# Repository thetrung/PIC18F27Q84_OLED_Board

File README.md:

PIC18F27Q84 OLED Playboard
==============================
Nothing much to say, just for entertainment & satisfy myself for designing things in my head.

### Overview ::
**MCU SPECS:** 64Mhz - 128KB Flash - 8KB SRAM - 1KB EEPROM. 
Detailed information on [Microchip](https://www.microchip.com/en-us/product/pic18f27q43).

The board was made with intention to resemble tiny game consoles with proper input / output, which I got inspired by ATTiny85 board. It has :

- 1x Speaker
- 1x Power slide.
- 4x Buttons Input.
- 10x LEDs on Top Row.
- 4x LEDs above all buttons.
- 1x LEDs to indicate power state.
- 1x LED for STATUS (anything you want).
- ICSP to Program with Microchip PICKIT 3/4/5.
- OLED 128x32 Module support pins (SDA/SCK/VCC/GND).

- The 3V Battery Holder can be installed on the back. Although I'm not sure if it can actually run since got nothing to test but any compatible coin-battery should work somehow (CR2032, LIR2032... but I aim for CR2450). Turn off any unused / unnecessary modules inside your PIC & outside the board to save power on battery. I only tested this dual power system via simulator mostly :

### Schematic ::

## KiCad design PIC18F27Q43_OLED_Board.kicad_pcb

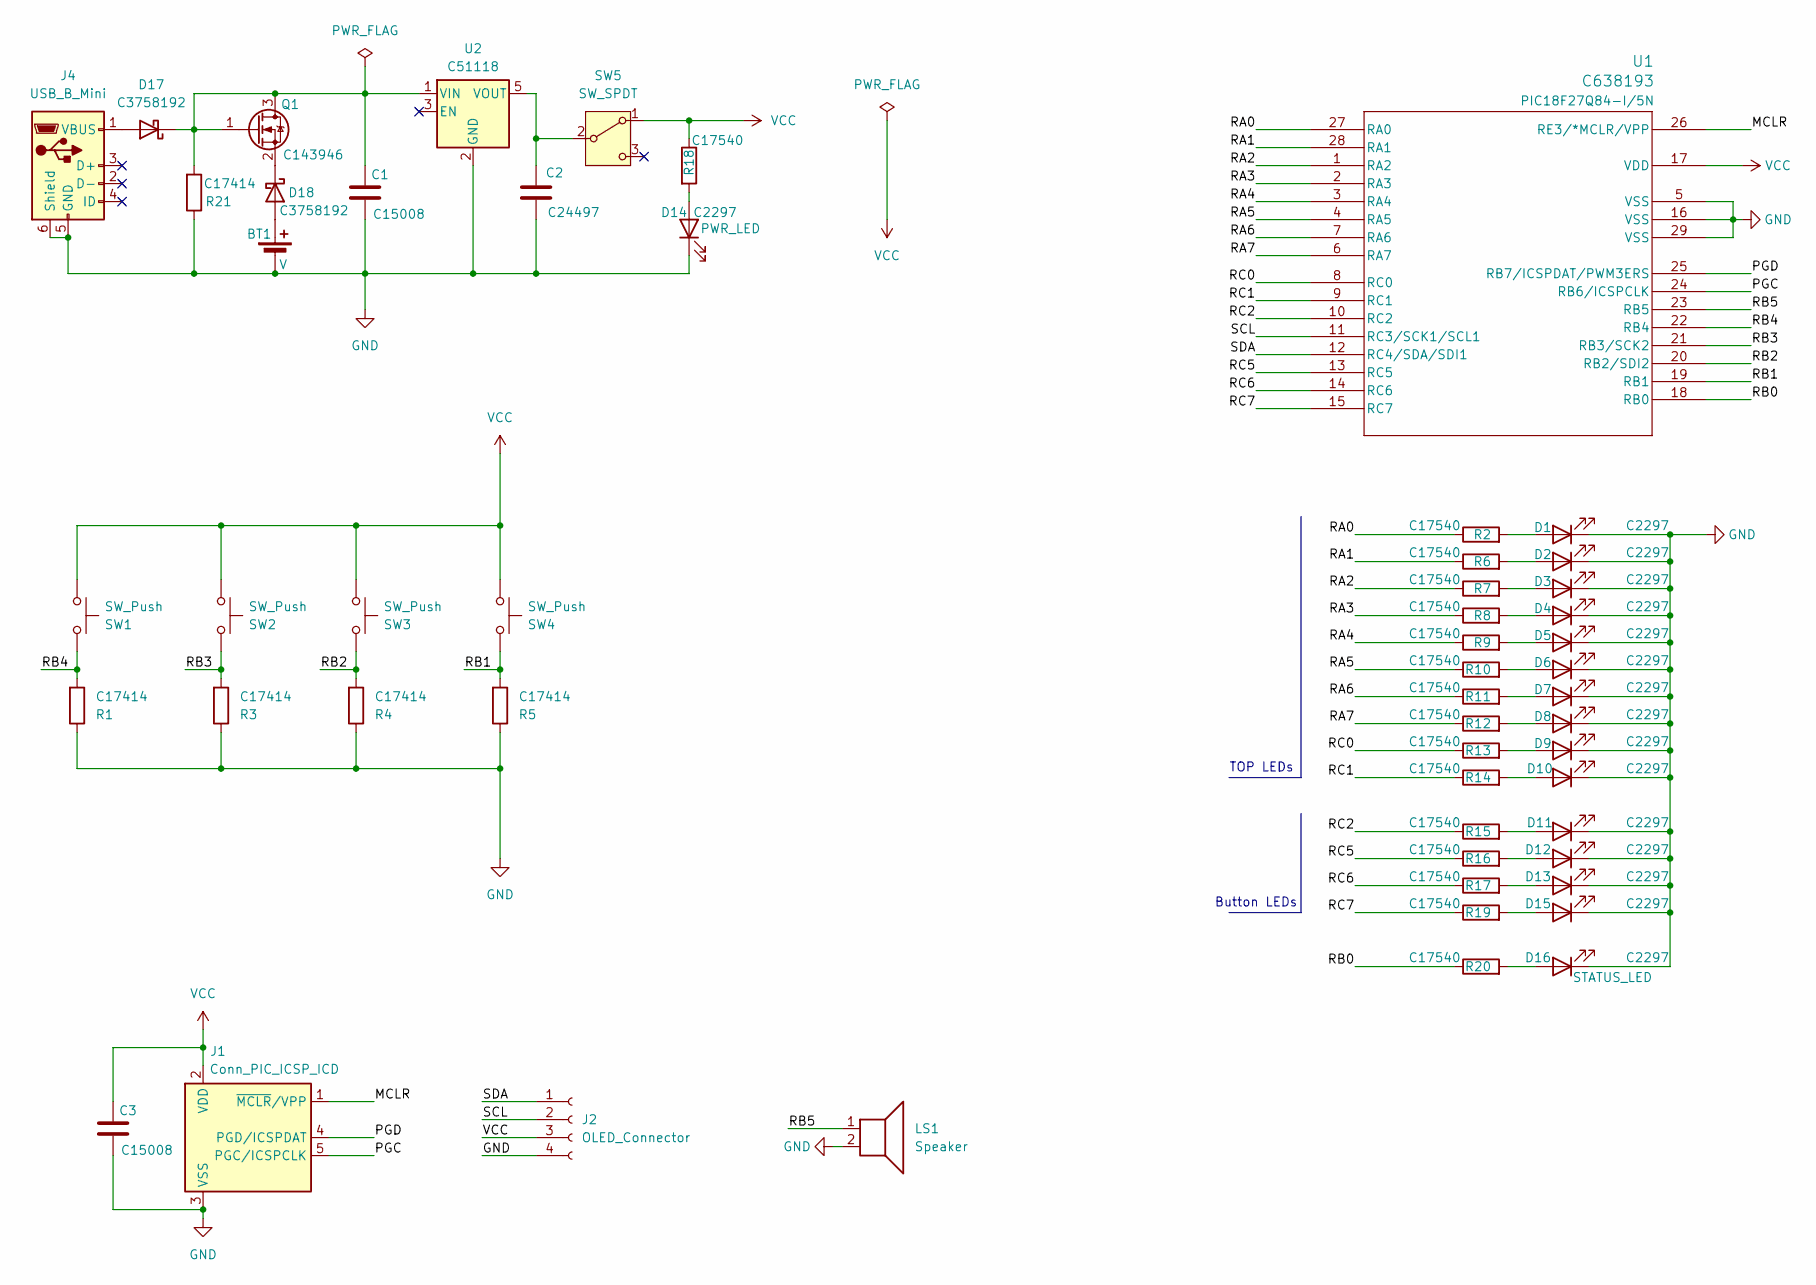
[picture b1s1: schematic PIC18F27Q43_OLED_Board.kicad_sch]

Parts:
BT1: V; BatteryHolder_ComfortableElectronic_CH273-2450_1x2450
C1, C3: C15008; C_1206_3216Metric
C2: C24497; C_1206_3216Metric
D1, D2, D3, D4, D5, D6, D7, D8, D9, D10, D11, D12, D13, D14, D15, D16: C2297; LED_0805_2012Metric
D17, D18: C3758192; D_0603_1608Metric
J1: Conn_PIC_ICSP_ICD; PinHeader_1x05_P2.54mm_Vertical
J2: OLED_Connector; PinHeader_1x04_P2.54mm_Vertical
J4: USB_B_Mini; USB_Mini-B_Tensility_54-00023_Vertical
LS1: Speaker; Buzzer_12x9.5RM7.6
Q1: C143946; SOT-23
R1, R3, R4, R5, R21: C17414; R_0805_2012Metric
R2, R6, R7, R8, R9, R10, R11, R12, R13, R14, R15, R16, R17, R18, R19, R20: C17540; R_0805_2012Metric
SW1, SW2, SW3, SW4: SW_Push; SW_PUSH_6mm_H5mm
SW5: SW_SPDT; SW_Slide_SPDT_Straight_CK_OS102011MS2Q
U1: C638193; VQFN28_5N_MCH
U2: C51118; SOT-23-5

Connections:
/MCLR: J1.1 (~MCLR/VPP), U1.26 (RE3/*MCLR/VPP)
/PGC: J1.5 (PGC/ICSPCLK), U1.24 (RB6/ICSPCLK)
/PGD: J1.4 (PGD/ICSPDAT), U1.25 (RB7/ICSPDAT/PWM3ERS)
/RA0: R2.1, U1.27 (RA0)
/RA1: R6.1, U1.28 (RA1)
/RA2: R7.1, U1.1 (RA2)
/RA3: R8.1, U1.2 (RA3)
/RA4: R9.1, U1.3 (RA4)
/RA5: R10.1, U1.4 (RA5)
/RA6: R11.1, U1.7 (RA6)
/RA7: R12.1, U1.6 (RA7)
/RB0: R20.1, U1.18 (RB0)
/RB1: R5.2, SW4.1, U1.19 (RB1)
/RB2: R4.2, SW3.1, U1.20 (RB2/SDI2)
/RB3: R3.2, SW2.1, U1.21 (RB3/SCK2)
/RB4: R1.2, SW1.1, U1.22 (RB4)
/RB5: LS1.1, U1.23 (RB5)
/RC0: R13.1, U1.8 (RC0)
/RC1: R14.1, U1.9 (RC1)
/RC2: R15.1, U1.10 (RC2)
/RC5: R16.1, U1.13 (RC5)
/RC6: R17.1, U1.14 (RC6)
/RC7: R19.1, U1.15 (RC7)
/SCL: J2.2, U1.11 (RC3/SCL1/SCK1)
/SDA: J2.1, U1.12 (RC4/SDA/SDI1)
GND: BT1.2 (-), C1.2, C2.2, C3.2, D1.1 (K), D2.1 (K), D3.1 (K), D4.1 (K), D5.1 (K), D6.1 (K), D7.1 (K), D8.1 (K), D9.1 (K), D10.1 (K), D11.1 (K), D12.1 (K), D13.1 (K), D14.1 (K), D15.1 (K), D16.1 (K), J1.3 (VSS), J2.4, J4.5 (GND), J4.6 (Shield), LS1.2, R1.1, R3.1, R4.1, R5.1, R21.1, U1.5 (VSS), U1.16 (VSS), U1.29 (VSS), U2.2 (GND)
unnamed: BT1.1 (+), D18.2 (A)
unnamed: D1.2 (A), R2.2
unnamed: D2.2 (A), R6.2
unnamed: D3.2 (A), R7.2
unnamed: D4.2 (A), R8.2
unnamed: D5.2 (A), R9.2
unnamed: D6.2 (A), R10.2
unnamed: D7.2 (A), R11.2
unnamed: D8.2 (A), R12.2
unnamed: D9.2 (A), R13.2
unnamed: D10.2 (A), R14.2
unnamed: D11.2 (A), R15.2
unnamed: D12.2 (A), R16.2
unnamed: D13.2 (A), R17.2
unnamed: D14.2 (A), R18.2
unnamed: D15.2 (A), R19.2
unnamed: D16.2 (A), R20.2
unnamed: D17.2 (A), J4.1 (VBUS)
unnamed: C1.1, D17.1 (K), Q1.1 (G), Q1.3 (D), R21.2, U2.1 (VIN)
unnamed: D18.1 (K), Q1.2 (S)
unnamed: C2.1, SW5.2 (B), U2.5 (VOUT)
VCC: C3.1, J1.2 (VDD), J2.3, R18.1, SW1.2, SW2.2, SW3.2, SW4.2, SW5.1 (A), U1.17 (VDD)

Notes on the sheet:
TOP LEDs
Button LEDs

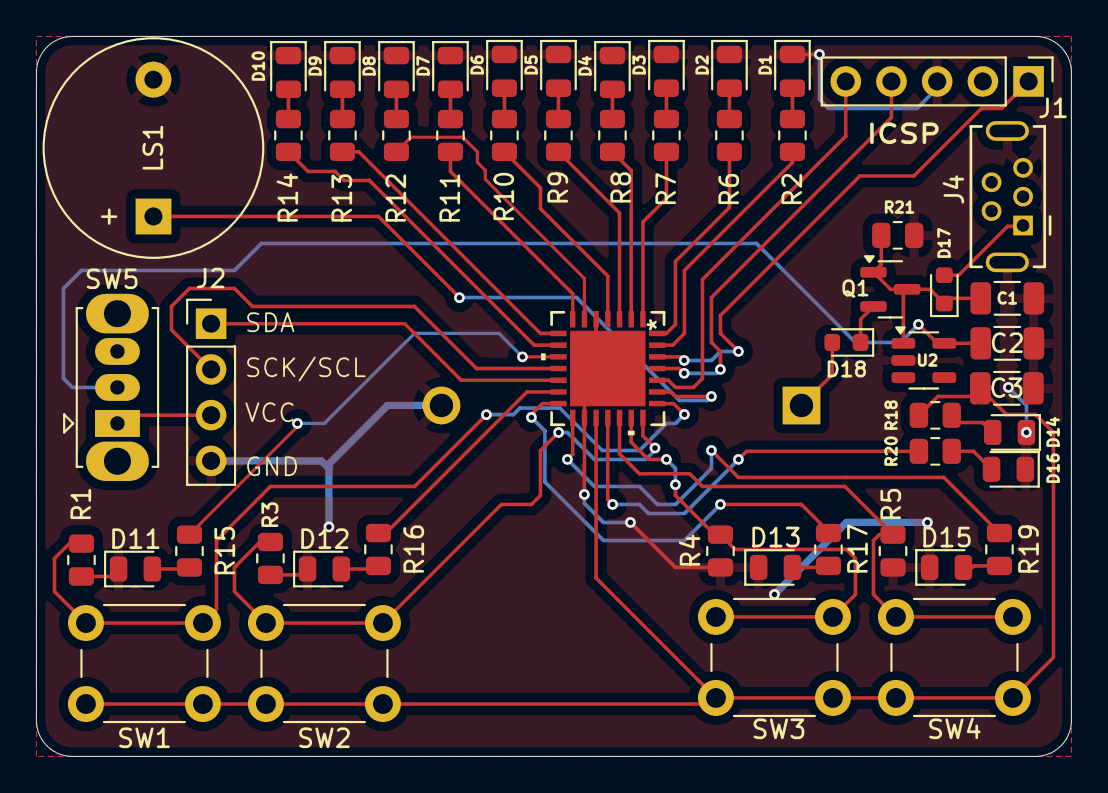
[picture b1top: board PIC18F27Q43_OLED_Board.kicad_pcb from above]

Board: 2 copper layers, 57.5 x 40.0 mm, 55 parts (1 on the bottom side), 48 nets.

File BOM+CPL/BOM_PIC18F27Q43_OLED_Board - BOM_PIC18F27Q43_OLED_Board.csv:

Comment,Designator,Footprint,LCSC Part Number
200Ω,"R6,R9,R11,R19,R15,R20,R17,R10,R14,R2,R12,R18,R7,R16,R13,R8",R_0805_2012Metric,C17540
10kΩ,"R21,R4,R5,R1,R3",R_0805_2012Metric,C17414
Emerald 0805 LED,"D2,D8,D1,D5,D11,D10,D16,D3,D9,D6,D15,D12,D14,D4,D13,D7",LED_0805_2012Metric,C2297
PIC18F27Q43-I/STX,U1,VQFN28_STX_MCH,C638193
100uF,"C1,C3",C_1206_3216Metric,C15008
40V 1A 550mV@700mA 0603 Schottky Diodes,"D18,D17",D_0603_1608Metric,C3758192
"20V 6.3A 21mΩ@4.5V,6.3A 1.3W 900mV 1 N-channel SOT-23 MOSFETs ROHS",Q1,SOT-23,C143946
LDO 65dB@(1kHz) 600mA Fixed 3.3V Positive electrode 6V SOT-25-5 Voltage Regulators,U2,SOT-23-5,C51118
100nF,C2,C_1206_3216Metric,C24497

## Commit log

2025-03-27 Init Board
2025-03-27 Finished SCHfor VEXT + VBAT
2025-03-27 Rev.1 : PCB Design finished.
2025-03-27 Refine Silkscreen
2025-03-27 Add images
2025-03-28 Ready for PCBA
2025-03-28 move from Q43 -> Q84 due to chip shortage
2025-03-28 Finished Routing to new Q84
2025-03-28 Corrected BOM+CPL & Updated Images
2025-04-02 update symbol
